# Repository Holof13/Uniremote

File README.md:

### UNIREMOTE

Uniremote is a simple project with the objective of making a simple IR remote to control non-smart home appliances with Homeassistant. The system is powered by an ESP-01 and has programming ports.

DISCLAMER: This project is still in development.

TODO:
  -Design a case for it in FreeCAD for 3D Printing.

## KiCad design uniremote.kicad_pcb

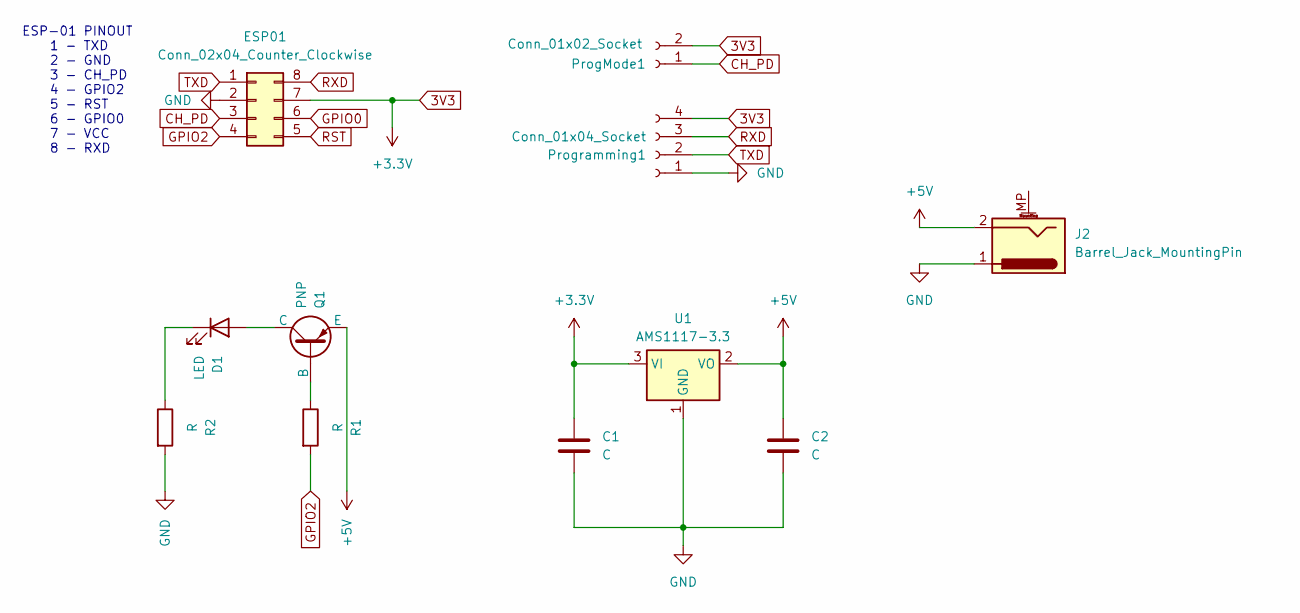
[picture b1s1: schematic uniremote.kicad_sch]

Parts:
C1, C2: C; C_Disc_D3.0mm_W1.6mm_P2.50mm
D1: LED; LED_D5.0mm_Horizontal_O1.27mm_Z3.0mm
ESP01: Conn_02x04_Counter_Clockwise; PinHeader_2x04_P2.54mm_Vertical
J2: Barrel_Jack_MountingPin; BarrelJack_Kycon_KLDX-0202-xC_Horizontal
ProgMode1: Conn_01x02_Socket; PinSocket_1x02_P2.54mm_Vertical
Programming1: Conn_01x04_Socket; PinSocket_1x04_P2.54mm_Vertical
Q1: PNP; TO-92
R1, R2: R; R_Axial_DIN0204_L3.6mm_D1.6mm_P5.08mm_Horizontal
U1: AMS1117-3.3; SOT-223-3_TabPin2

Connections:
3V3: C1.1, ESP01.7, ProgMode1.2, Programming1.4, U1.3 (VI)
+5V: C2.1, J2.2, Q1.3 (E), U1.2 (VO)
CH_PD: ESP01.3, ProgMode1.1
GND: C1.2, C2.2, ESP01.2, J2.1, Programming1.1, R2.2, U1.1 (GND)
GPIO0: ESP01.6
GPIO2: ESP01.4, R1.2
unnamed: D1.2 (A), Q1.1 (C)
unnamed: D1.1 (K), R2.1
unnamed: Q1.2 (B), R1.1
RST: ESP01.5
RXD: ESP01.8, Programming1.3
TXD: ESP01.1, Programming1.2

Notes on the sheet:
ESP-01 PINOUT 1 - TXD 2 - GND 3 - CH_PD 4 - GPIO2 5 - RST 6 - GPIO0 7 - VCC 8 - RXD

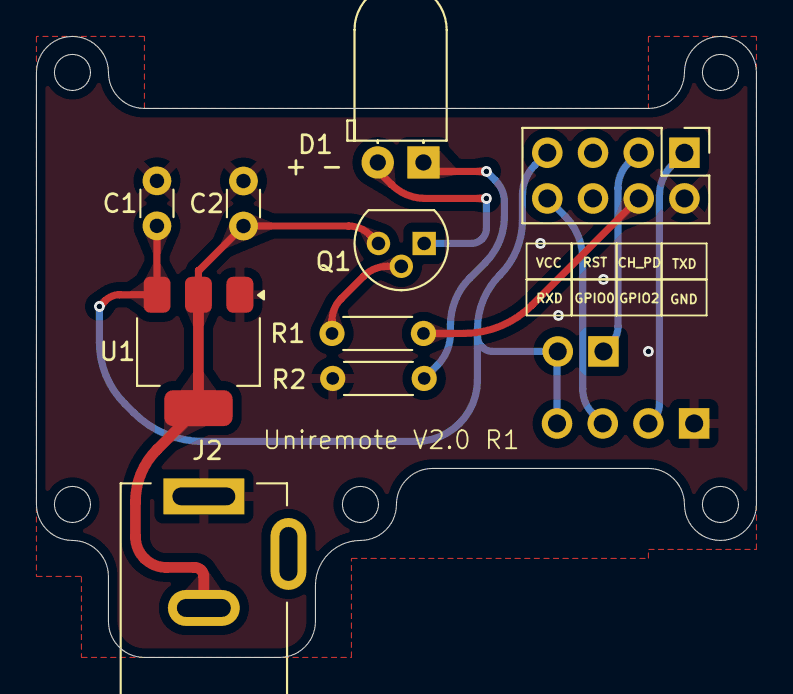
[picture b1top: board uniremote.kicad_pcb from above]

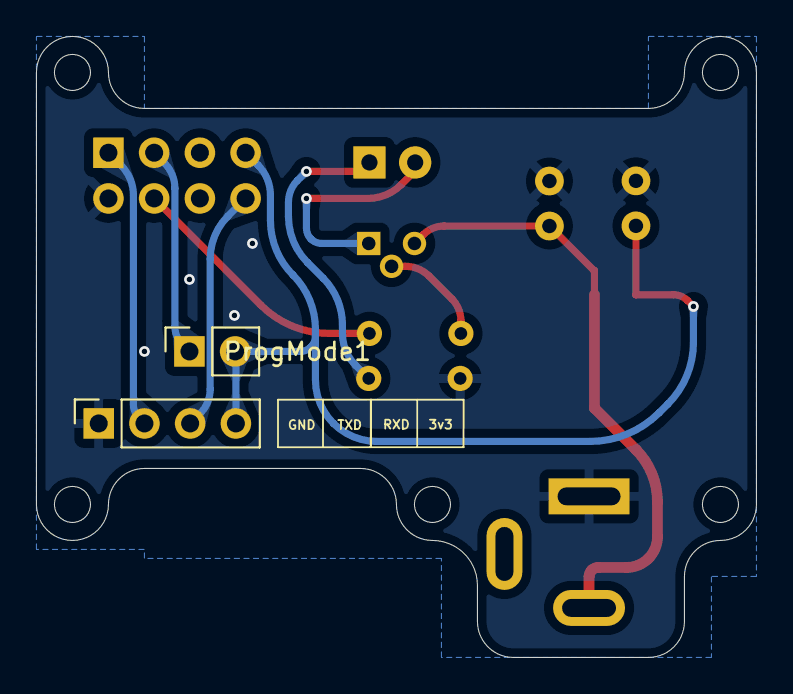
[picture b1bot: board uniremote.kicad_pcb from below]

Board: 2 copper layers, 40.0 x 34.5 mm, 11 parts (2 on the bottom side), 10 nets.
